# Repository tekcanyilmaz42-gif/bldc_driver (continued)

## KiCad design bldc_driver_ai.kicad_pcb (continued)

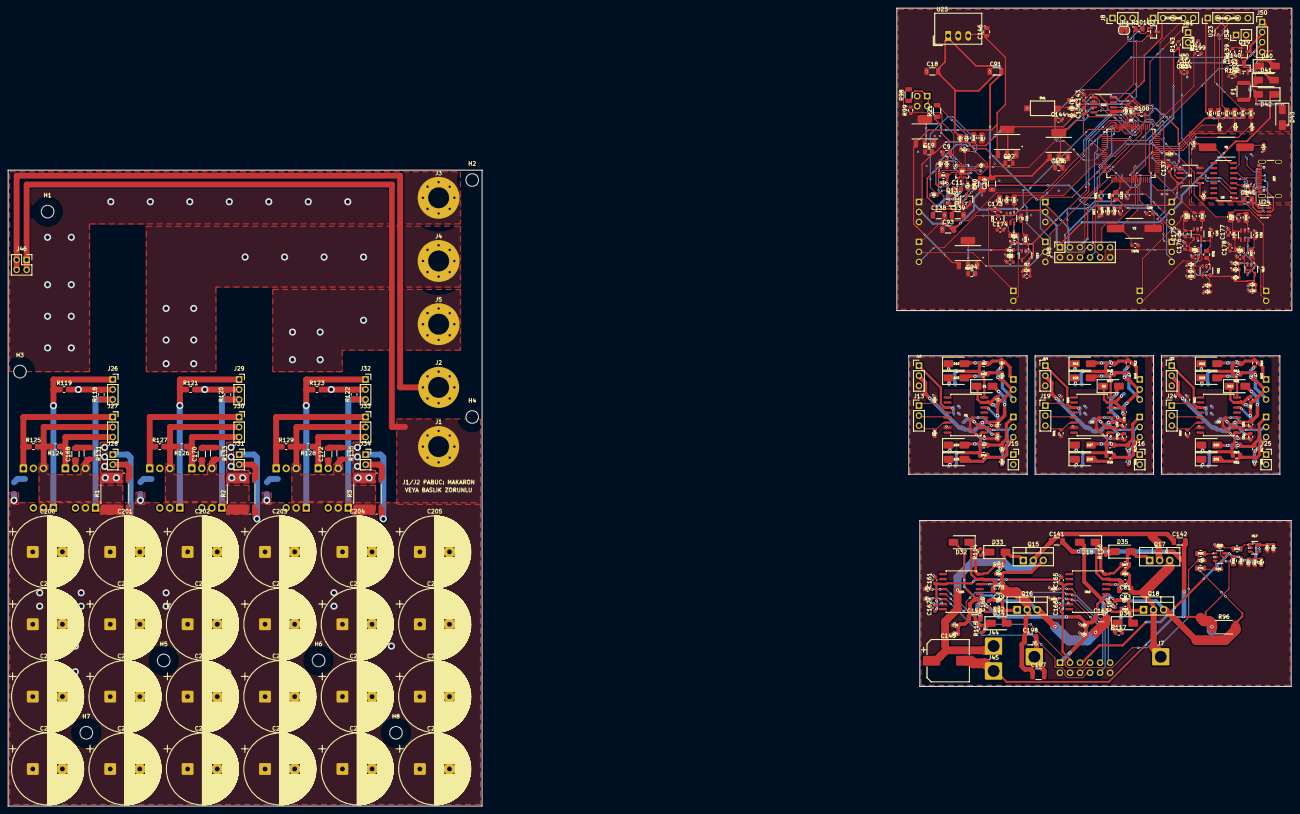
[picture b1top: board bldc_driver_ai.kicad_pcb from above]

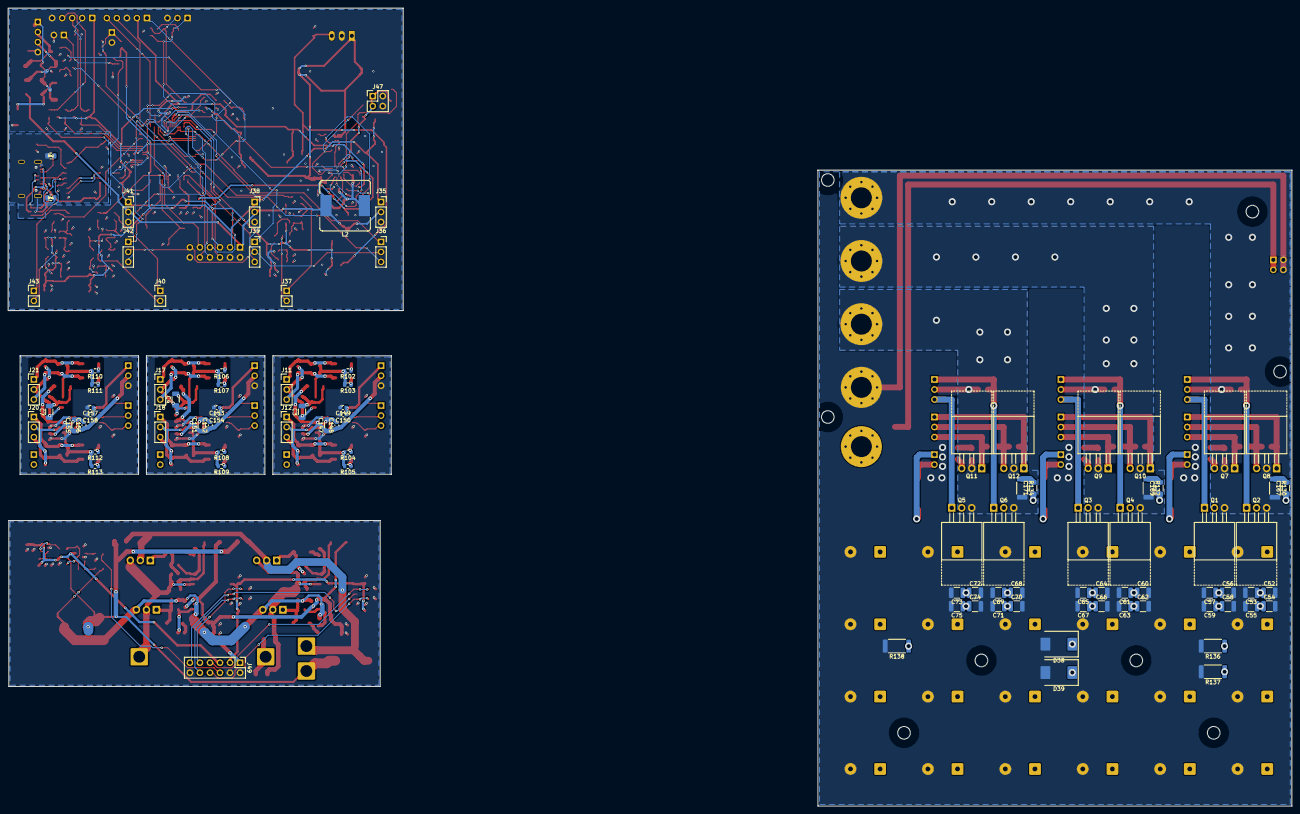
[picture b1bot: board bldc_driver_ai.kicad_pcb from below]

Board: 2 copper layers, 325.0 x 202.0 mm, 460 parts (94 on the bottom side), 177 nets.

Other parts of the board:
H1, H2, H3, H4, H5, H6, H7, H8: M3_Sogutucu; MountingHole_3.2mm_M3

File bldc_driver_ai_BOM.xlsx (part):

bldc_driver_ai – Malzeme Listesi (BOM)
Rev 2.5 (2 katman). Kaynak: bldc_driver_ai.kicad_pcb, referans format: yardımcı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
Üretilecek set sayısı: |  |  | 1 |  | Sarı hücreler (set sayısı, birim fiyat) kullanıcı girişidir. Yeşil = referans B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
şematik | footprint | No | Kart / Modül | Referanslar | Adet / set | Değer | Kılıf (footprint) | Üretici parça no (MPN) | Üretici | Açıklama | Tedarikçi | Ürün arama | Datasheet | Toplam adet | Birim fiyat (TL) | Toplam fiyat (TL) | Not
 |  |  | 1 - Güç kartı
 |  | 1 | Güç kartı | Q1, Q2, Q3, Q4, Q5, Q6, Q7, Q8, Q9, Q10, Q11, Q12 | 12 | IRFB4110PBF | TO-220-3_Horizontal_TabUp_NoHole | IRFB4110PBF | Infineon | N-kanal MOSFET 100 V, 4.5 mΩ, TO-220AB | DigiKey / Özdisan | DigiKey'de ara | irfb4110pbf.pdf |  |  |  | DI101N10PQ yerine (Rev 3.0). Güç kartında kartın altında yatık, tab soğutucuya 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
 |  | 2 | Güç kartı | D38, D39 | 2 | 5.0SMDJ58CA | D_SMC | 5.0SMDJ58CA | Littelfuse | TVS diyot 58 V çift yönlü 5000 W, SMC | DigiKey | DigiKey'de ara | 5.0SMDJ series datasheet |  |  |  | Referanstaki SMCJ58A yerine daha yüksek enerjili TVS (bara koruması, Faz 3)
 |  | 3 | Güç kartı | C52, C53, C54, C55, C56, C57, C58, C59, C60, C61, C62, C63, C64, C65, C66, C67,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 | 24 | 4.7uF/100V | C_1210 | HMK325C7475KN-TE | Taiyo Yuden | MLCC 4.7 µF 100 V X7S 1210 (bara seramik) | DigiKey | DigiKey'de ara | GRM32E datasheet |  |  |  | Faz başına yüksek frekans bara dekuplajı (Faz 3)
 |  | 4 | Güç kartı | C167, C168, C169, C170, C171, C172 | 6 | 4.7nF/100V C0G | C_1206 | GRM3195C2A472JA01D | Murata | MLCC 4.7 nF 100 V C0G 1206 (snubber) | DigiKey | DigiKey'de ara | GRM319 datasheet |  |  |  | RC snubber (Faz 3)
 |  | 5 | Güç kartı | C200, C201, C202, C203, C204, C205, C206, C207, C208, C209, C210, C211, C212, C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 | 24 | 1000uF/100V | CP_Radial_D18.0mm_L40mm_P7.50mm_KOSHIN_KLH | PKLH-100V102MK400 | KOSHIN | Alüminyum elektrolitik 1000 µF ±%20 100 V, KLH serisi, Ø18 x 40 mm radyal, P 7.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 | Özdisan | DigiKey'de ara | KLH-100V102MK400.pdf (KOSHIN DJJ-2875) |  |  |  | Kullanıcı seçimi: TDK B32776G4506 film yerine. Güç kartının sağ bölümünde, pete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
 |  | 6 | Güç kartı | R1, R2, R3 | 3 | 0.2mR 4-terminal | R_Shunt_Isabellenhuette_BVR4026 | BVR-Z-R0002-1.0 | Isabellenhütte | 4 uçlu (Kelvin) şönt 0.2 mΩ %1, 4026 | DigiKey / Mouser | DigiKey'de ara | BVR datasheet |  |  |  | Faz 3: HoLRS2512 yerine 4 uçlu şönt; 100 A rms'de I²R ≈ 2 W. MPN son ekini dist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
 |  | 7 | Güç kartı | R118, R119, R120, R121, R122, R123, R124, R125, R126, R127, R128, R129 | 12 | 10k | R_0805 | RC0603JR-0710KL | YAGEO | Direnç 10 kΩ %5 0603 | Özdisan | DigiKey'de ara | PYu-RC_Group_51_RoHS_L_10.pdf
 |  | 8 | Güç kartı | R130, R132, R134 | 3 | 2.2 | R_2010 | CRCW20102R20FKEF | Vishay | Direnç 2.2 Ω %1 0.75 W 2010 (yüksek taraf RC snubber) | DigiKey | DigiKey'de ara | dcrcwe3.pdf |  |  |  | HS snubber, alt yüzde band içinde; kayıp ≈ 0.27 W
 |  | 9 | Güç kartı | R131, R133, R135 | 3 | 2.2 | R_1210 | CRCW12102R20FKEA | Vishay | Direnç 2.2 Ω %1 0.5 W 1210 (alçak taraf RC snubber) | DigiKey | DigiKey'de ara | dcrcwe3.pdf |  |  |  | LS snubber; band üstüne sığması için 2010 yerine 1210 (kayıp ≈ 0.27 W)
 |  | 10 | Güç kartı | R136, R137, R138 | 3 | 10k 1W | R_2512 | CRCW251210K0FKEG | Vishay | Direnç 10 kΩ %1 1 W 2512 (bara deşarj) | DigiKey | DigiKey'de ara | dcrcwe3.pdf |  |  |  | Bara kapasitörü deşarj (bleeder), Faz 3
 |  | 11 | Güç kartı | J28, J31, J34 | 3 | - | PinSocket_1x02 | - | genel | 2.54 mm dişi soket 1x2, 8.5 mm gövde | genel (Motorobit / Özdisan) |  | - |  |  |  | Kartlar arası konnektör
 |  | 12 | Güç kartı | J26, J27, J29, J30, J32, J33 | 6 | - | PinSocket_1x03 | - | genel | 2.54 mm dişi soket 1x3, 8.5 mm gövde | genel (Motorobit / Özdisan) |  | - |  |  |  | Kartlar arası konnektör
 |  | 13 | Güç kartı | J46 | 1 | - | PinSocket_2x02 | - | genel | 2.54 mm dişi soket 2x2, 8.5 mm gövde – riser | genel (Motorobit / Özdisan) |  | - |  |  |  | Kartlar arası konnektör
 |  |  | 2 - Gate driver (U/V/W)
 |  | 14 | Gate driver (U/V/W) | U1, U2, U3 | 3 | IR2110S | SOIC-16W_7.5x10.3mm_P1.27mm | IR2110STRPBF | Infineon | Yüksek/alçak taraf gate sürücü, SOIC-16W | Motorobit | DigiKey'de ara | IR2110(-1-2)(S)PbF
 |  | 15 | Gate driver (U/V/W) | D10, D11, D12, D23, D24, D25, D26, D27, D28, D29, D30, D31 | 12 | SS18 | D_SMA | SS18 | onsemi | Schottky diyot 1 A 80 V, SMA | Özdisan | DigiKey'de ara | SK12-SK110 |  |  |  | VCC-VB (bootstrap) ve gate deşarj diyotu olarak kullanılıyor
 |  | 16 | Gate driver (U/V/W) | D1, D2, D13 | 3 | US1D | D_SMA | US1D-E3/61T | Vishay | Ultra hızlı diyot 1 A 200 V, SMA | DigiKey | DigiKey'de ara | US1A-US1M datasheet |  |  |  | Bootstrap diyodu (SS18 yerine, Faz 2)
 |  | 17 | Gate driver (U/V/W) | C1, C5, C6, C148, C149, C152, C153, C156, C157 | 9 | 100nF | C_0603 | CL10B104KB8NNNC | Samsung | MLCC 100 nF 50 V X7R 0603 | Özdisan | DigiKey'de ara | SAMSUNG MLCC_JAN-2024.pdf
 |  | 18 | Gate driver (U/V/W) | C3, C4, C7 | 3 | 2.2uF/25V | C_1206 | CL31B225KAHNNNE | Samsung | MLCC 2.2 µF 25 V X7R 1206 | Özdisan | DigiKey'de ara | SAMSUNG MLCC_JAN-2024.pdf |  |  |  | Revizyonla eklendi
 |  | 19 | Gate driver (U/V/W) | C41, C47, C48, C49, C50, C51, C150, C154, C158 | 9 | 1uF | C_0603 | C0603X5R105K250NT | OEM | MLCC 1 µF 25 V X5R 0603 | Özdisan | DigiKey'de ara | -
 |  | 20 | Gate driver (U/V/W) | C147, C151, C155 | 3 | 22uF/25V | C_1206 | CL31A226KAHNNNE | Samsung | MLCC 22 µF 25 V X5R 1206 | Özdisan | DigiKey'de ara | SAMSUNG MLCC_JAN-2024.pdf |  |  |  | Gate sürücü VCC dekuplajı
 |  | 21 | Gate driver (U/V/W) | R6, R7, R10, R11, R14, R15, R43, R45, R47, R48, R51, R52 | 12 | 10 | R_0805 | 0805S8J0100T5E | ROYALOHM | Direnç 10 Ω %5 0805 (gate direnci) | Özdisan | DigiKey'de ara | general_royalohm.pdf
 |  | 22 | Gate driver (U/V/W) | R8, R9, R12, R13, R16, R17, R44, R46, R49, R50, R53, R54, R58, R59, R60, R61, R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 | 18 | 10k | R_0603 | RC0603JR-0710KL | YAGEO | Direnç 10 kΩ %5 0603 | Özdisan | DigiKey'de ara | PYu-RC_Group_51_RoHS_L_10.pdf
 |  | 23 | Gate driver (U/V/W) | R102, R103, R104, R105, R106, R107, R108, R109, R110, R111, R112, R113 | 12 | 2.2 | R_0603 | WR06X2R2 JGL | WALSIN | Direnç 2.2 Ω %5 0603 | Özdisan | DigiKey'de ara | ASC_WR_V32
 |  | 24 | Gate driver (U/V/W) | J10, J11, J12, J13, J14, J17, J18, J19, J20, J21, J22, J24 | 12 | - | PinHeader_1x03 | - | genel | 2.54 mm erkek pin başlık 1x3, düz | genel (Motorobit / Özdisan) |  | - |  |  |  | Kartlar arası konnektör
 |  | 25 | Gate driver (U/V/W) | J15, J16, J25 | 3 | - | PinSocket_1x02 | ESQ-102-xx-T-S sınıfı (uzun kuyruklu) | Samtec / genel | 2.54 mm 1x2 STACKING dişi soket: üstte 8.5 mm soket, altta ≥ 10.5 mm uzun kuyru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 | Samtec / LCSC | DigiKey'de ara | - |  |  |  | Faz 7 (inceleme K21): şönt ölçüm hattı güç kartı J28/J31/J34 soketlerine bu kuy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
 |  |  | 3 - Kontrol kartı
 |  | 26 | Kontrol kartı | Q13, Q14 | 2 | IRLML0100TRPBF | SOT-23 | IRLML0100TRPBF | Infineon | N-kanal MOSFET 100 V 1.6 A, SOT-23 | DigiKey | DigiKey'de ara | IRLML0100 datasheet |  |  |  | Faz 2
 |  | 27 | Kontrol kartı | Q19, Q20 | 2 | AO3400A | SOT-23 | AO3400A | Alpha & Omega | N-kanal MOSFET 30 V 5.7 A, SOT-23 | DigiKey | DigiKey'de ara | AO3400A datasheet |  |  |  | Kontaktör / ön şarj sürücüsü
 |  | 28 | Kontrol kartı | U4 | 1 | ADuM1201 | ADuM1201_LP | ADUM1201ARZ | Analog Devices | Çift kanallı dijital izolatör, SOIC-8 | DigiKey | DigiKey'de ara | ADuM1200/ADuM1201 (Rev.L) |  |  |  | Referans BOM'da CJMCU-1201 modülü var; kart üstü SOIC-8 entegre gerekir
 |  | 29 | Kontrol kartı | U5 | 1 | CH340G | CH340G_LP | CH340G | WCH | USB-UART dönüştürücü, SOP-16 | Motorobit | DigiKey'de ara | ch340g-datasheet
 |  | 30 | Kontrol kartı | U6 | 1 | dsPIC33CK256MP508 | LQFP-80_12x12mm_P0.5mm | DSPIC33CK256MP508-I/PT | Microchip Technology | dsPIC33CK DSC, 256 KB, TQFP-80 12x12 | DigiKey | DigiKey'de ara | dsPIC33CK256MP508 Family Data Sheet |  |  |  | Referans BOM'da MP506 (64 pin) yazıyor; tasarım 80 pinli MP508 kullanıyor
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
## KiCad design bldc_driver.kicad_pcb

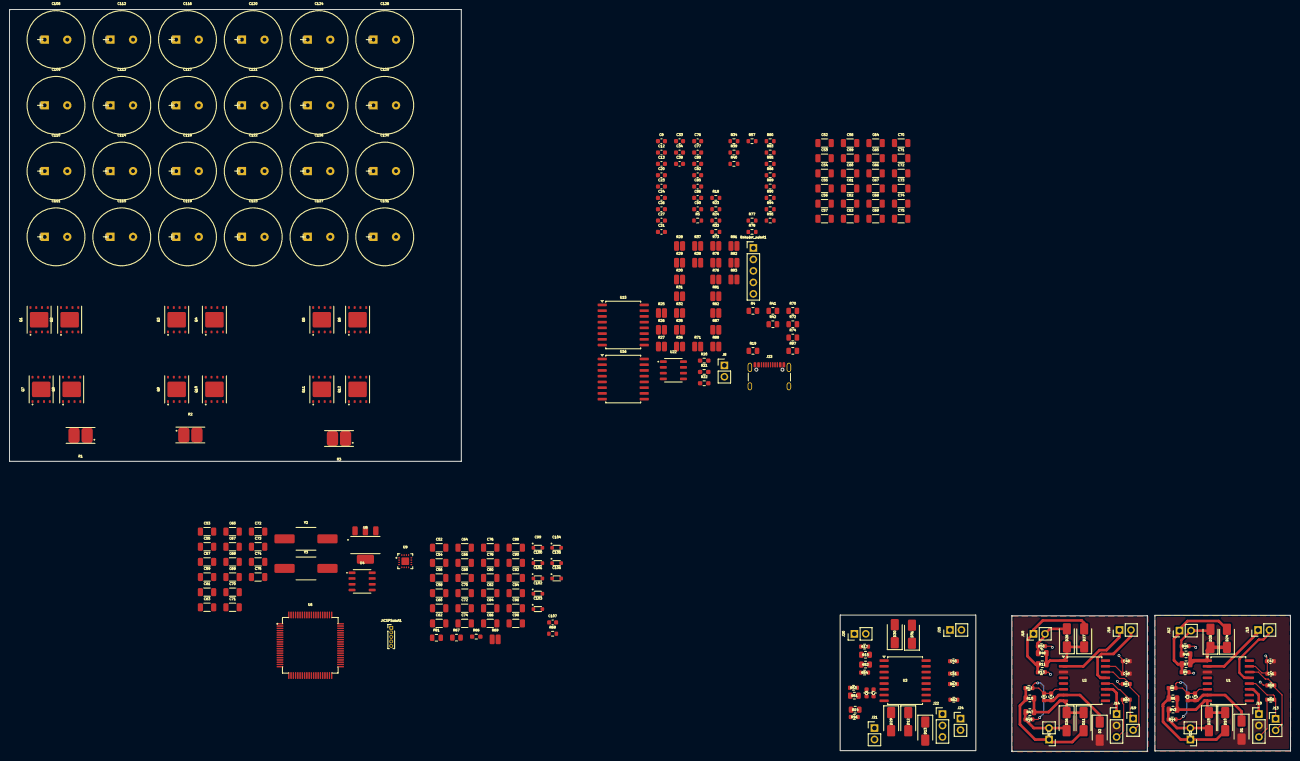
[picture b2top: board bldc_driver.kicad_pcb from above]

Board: 2 copper layers, 283.5 x 164.2 mm, 277 parts (0 on the bottom side), 102 nets.

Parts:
C1, C5, C6: 100nF; C_0603_1608Metric
C3, C4, C7: 10uF; C_0603_1608Metric
C8: 10nF; C_0603_1608Metric
C12: 4.7nF; C_0603_1608Metric
C13, C20, C31, C38, C41, C47, C48, C49, C50, C51, C76#2, C77, C80#2, C82#2, C90, C107: 1uF; C_0603_1608Metric
C23, C24, C26, C27, C33, C34, C85, C86: 1nF; C_0603_1608Metric
C52, C52#2, C53, C53#2, C54, C54#2, C55, C55#2, C56, C56#2, C57, C57#2, C58, C58#2, C59, C59#2, C60, C60#2, C61, C61#2, C62, C62#2, C63, C63#2, C64, C64#2, C65, C65#2, C66, C66#2, C67, C67#2, C68, C68#2, C68#3, C69, C69#2, C70, C70#2, C70#3, C71, C71#2, C72, C72#2, C72#3, C73, C73#2, C74, C74#2, C74#3, C75, C75#2, C76, C78, C80, C82, C84, C86#2, C88, C90#2, C92, C94, C96, C98: 2.2uF; C_1206_3216Metric
C99, C101: 20pF; CL10B104KB8NNNC
C100, C102, C103, C104, C105, C106: 100nF; CL10B104KB8NNNC
C108, C109, C110, C111, C112, C113, C114, C115, C116, C117, C118, C119, C120, C121, C122, C123, C124, C125, C126, C127, C128, C129, C130, C131: 470uF; KLH-063V471MH200-TA5.0
D1, D2, D10, D11, D12, D13, D23, D24, D25, D26, D27, D28, D29, D30, D31: SS18; D_SMA
Enkoder_soket1: Conn_01x05_Socket; PinHeader_1x05_P2.54mm_Vertical
FB1: FerriteBead; C_0805_2012Metric
J8: CAN-bus; PinHeader_1x02_P2.54mm_Vertical
J10, J14, J22: Conn_01x03_Pin; PinHeader_1x03_P2.54mm_Vertical
J11, J12, J13, J15, J16, J17, J18, J19, J20, J21, J24, J25: Conn_01x02_Pin; PinHeader_1x02_P2.54mm_Vertical
J23: USB_IN; USB_C_Receptacle_GCT_USB4105-xx-A_16P_TopMnt_Horizontal
JICSPSoket1: Conn_01x05_Pin; PinHeader_1x05_P1.00mm_Vertical
Q1, Q2, Q3, Q4, Q5, Q6, Q7, Q8, Q9, Q10, Q11, Q12: DI101N10PQ
R1, R2, R3: HoLRS2512
R4, R70, R72, R74: 1.5k; R_0805_2012Metric
R5: 36k; R_0603_1608Metric
R6, R7, R10, R11, R14, R15, R43, R45, R47, R48, R51, R52: 10; R_0805_2012Metric
R8, R9, R12, R13, R16, R17, R23, R24, R33, R34, R39, R40, R44, R46, R49, R50, R53, R54, R57, R58, R59, R60, R61, R62, R63, R68, R77, R78, R80, R83, R85, R86, R89, R90, R94, R95: 10k; R_0603_1608Metric
R18: 20k; R_0603_1608Metric
R19, R67, R97: 1k; R_0805_2012Metric
R20: 2.2; R_0603_1608Metric_Pad0.98x0.95mm_HandSolder
R21, R66: 100k; R_0603_1608Metric_Pad0.98x0.95mm_HandSolder
R22: 60k; R_0603_1608Metric_Pad0.98x0.95mm_HandSolder
R25, R26, R27, R29, R30, R31, R35, R36, R37, R76, R81, R82, R87, R88, R91, R92: 10; R_0508_1220Metric_Pad1.12x2.15mm_HandSolder
R28, R32, R38, R69, R71, R73, R75, R93: 100; R_0508_1220Metric_Pad1.12x2.15mm_HandSolder
R41, R42: 5.1k; R_0805_2012Metric
U1, U2, U3, U15, U16: IR2110S; SOIC-16W_7.5x10.3mm_P1.27mm
U4: ADuM1201
U6: dsPIC33CK256MP508
U8: NCP1117
U9: MIC2128
U22: TJA1051
Y2, Y3: 12MHz Kristal; AS-12.000-18-3030-EXT-SMD-TR

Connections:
3V3: C20.2, C31.2, C38.2, C90.2, C102.2, C103.2, C104.2, C105.2, C106.2, C107.2, Enkoder_soket1.1, FB1.1, J10.1, J14.1, J22.1, JICSPSoket1.2, R23.2, R33.2, R39.2, R57.1, R68.2, R70.1, R72.1, R74.1, R94.2, U1.11 (VDD), U2.11 (VDD), U3.11 (VDD), U4.8 (VDD2), U6.12 (VDD), U6.31 (VDD), U6.51 (VDD), U6.71 (VDD), U8.2 (VO), U8.4 (TAB), U15.11 (VDD), U16.11 (VDD), U22.5 (VIO)
5V: J23.A4 (VBUS), J23.A9 (VBUS), J23.B4 (VBUS), J23.B9 (VBUS), U4.1 (VDD1)
12V: C13.2, C41.2, C47.2, C48.2, C49.2, C50.2, C51.2, C76#2.2, C77.2, C80#2.2, C82#2.2, D1.2 (A), D2.2 (A), D13.2 (A), J10.2, J14.2, J22.2, U1.3 (VCC), U2.3 (VCC), U3.3 (VCC), U9.9 (EXTVDD), U15.3 (VCC), U16.3 (VCC)
CANH: J8.2, U22.7 (CANH)
CANL: J8.1, U22.6 (CANL)
Enkoder_A: R71.2, U6.54 (RD5/RP69)
Enkoder_A_soket: Enkoder_soket1.2, R70.2, R71.1
Enkoder_B: R73.2, U6.53 (RD6/RP70)
Enkoder_B_soket: Enkoder_soket1.3, R72.2, R73.1
Enkoder_Z: R75.2, U6.52 (RD7/RP71)
Enkoder_Z_soket: Enkoder_soket1.4, R74.2, R75.1
FB: C12.1, R5.1, R18.1, R19.2, U9.13 (FB)
GND_PC: C99.1, C101.1, J23.A1 (GND), J23.A12 (GND), J23.B1 (GND), J23.B12 (GND), R41.1, R42.1, U4.4 (GND1)
G_UH1: D10.2 (A), J11.1, Q1.4 (G), R6.2, R8.2
G_UH2: D23.2 (A), J11.2, Q2.4 (G), R43.2, R44.2
G_UH_IN: J13.1, R59.1, U1.12 (HIN), U6.4 (RE1)
G_UL1: D24.2 (A), J12.1, Q7.4 (G), R7.2, R9.2
G_UL2: D25.2 (A), J12.2, Q8.4 (G), R45.2, R46.2
G_UL_IN: J13.2, R58.2, U1.14 (LIN), U6.2 (RE0)
G_VH1: D11.2 (A), J17.1, Q3.4 (G), R10.2, R12.2
G_VH2: D26.2 (A), J17.2, Q4.4 (G), R47.2, R49.2
G_VH_IN: J19.1, R60.1, U2.12 (HIN), U6.19 (RE3)
G_VL1: D27.2 (A), J18.1, Q9.4 (G), R11.2, R13.2
G_VL2: D28.2 (A), J18.2, Q10.4 (G), R48.2, R50.2
G_VL_IN: J19.2, R61.2, U2.14 (LIN), U6.17 (RE2)
G_WH1: D12.2 (A), J21.1, Q5.4 (G), R14.2, R16.2
G_WH2: D29.2 (A), J21.2, Q6.4 (G), R51.2, R53.2
G_WH_IN: J24.1, R62.1, U3.12 (HIN), U6.24 (RE5)
G_WL1: D30.2 (A), J20.1, Q11.4 (G), R15.2, R17.2
G_WL2: D31.2 (A), J20.2, Q12.4 (G), R52.2, R54.2
G_WL_IN: J24.2, R63.2, U3.14 (LIN), U6.22 (RE4)
IF_L: C8.1, C13.1, C20.1, C24.1, C27.1, C31.1, C34.1, C38.1, C41.1, C47.1, C48.1, C49.1, C50.1, C51.1, C52.2, C53.2, C54.2, C55.2, C56.2, C57.2, C58#2.2, C59.2, C60.2, C61.2, C62#2.2, C63.2, C64.2, C65#2.2, C66.2, C67.2, C68#2.2, C69#2.2, C70#3.2, C71#2.2, C72#3.2, C73.2, C74#3.2, C75.2, C76#2.1, C77.1, C80#2.1, C82#2.1, C86.1, C90.1, C100.1, C102.1, C103.1, C104.1, C105.1, C106.1, C107.1, Enkoder_soket1.5, J10.3, J14.3, J22.3, JICSPSoket1.3, R9.1, R13.1, R17.1, R21.1, R22.1, R24.1, R27.2, R30.2, R34.1, R36.2, R40.1, R46.1, R50.1, R54.1, R58.1, R59.2, R60.2, R61.1, R62.2, R63.1, R67.1, R77.2, R78.1, R80.2, R83.1, R85.1, R86.1, R89.1, R90.1, R91.2, R95.1, R97.1, U1.15 (VSS), U2.15 (VSS), U3.15 (VSS), U4.5 (GND2), U6.11 (VSS), U6.26 (AVSS), U6.32 (VSS), U6.50 (VSS), U6.70 (VSS), U8.1 (GND/ADJ), U9.6 (PGND), U9.14 (AGND), U9.17 (EP), U15.15 (VSS), U16.15 (VSS), U22.2 (GND), U22.8 (S)
IN181_IFout: C86.2, R93.1, U6.23 (RA4)
IN181_Uout: C24.2, R28.1, U6.16 (RA0)
IN181_Vout: C27.2, R32.1, U6.41 (RB2/RP34)
IN181_Wout: C34.2, R38.1, U6.58 (RB7/RP39)
MCLR: JICSPSoket1.1, R69.1, U6.9 (MCLR)
unnamed: C12.2, R18.2
unnamed: C1.2, C3.2, D1.1 (K), U1.7 (VB)
unnamed: C4.2, C5.2, D2.1 (K), U2.7 (VB)
unnamed: D10.1 (K), D23.1 (K), R6.1, R43.1, U1.8 (HO)
unnamed: D11.1 (K), D26.1 (K), R10.1, R47.1, U2.8 (HO)
unnamed: D12.1 (K), D29.1 (K), R14.1, R51.1, U3.8 (HO)
unnamed: C6.2, C7.2, D13.1 (K), U3.7 (VB)
unnamed: D24.1 (K), D25.1 (K), R7.1, R45.1, U1.1 (LO)
unnamed: D27.1 (K), D28.1 (K), R11.1, R48.1, U2.1 (LO)
unnamed: D30.1 (K), D31.1 (K), R15.1, R52.1, U3.1 (LO)
unnamed: R81.2, R85.2
unnamed: R81.1, U15.8 (HO)
unnamed: R82.2, R86.2
unnamed: R82.1, U15.1 (LO)
unnamed: R87.2, R89.2
unnamed: R87.1, U16.8 (HO)
unnamed: R88.2, R90.2
unnamed: R88.1, U16.1 (LO)
unnamed: J23.A5 (CC1), R41.2
unnamed: J23.B5 (CC2), R42.2
unnamed: R4.2, U9.3 (SW)
unnamed: R19.1, R97.2
unnamed: R68.1, R69.2
unnamed: J23.A6 (D+), J23.B6 (D+)
unnamed: J23.A7 (D-), J23.B7 (D-)
unnamed: FB1.2, U6.25 (AVDD)
unnamed: C23.2, R26.1
unnamed: C23.1, R27.1
unnamed: R21.2, R22.2, U9.11 (FREQ)
unnamed: R4.1, U9.2 (ILIM)
unnamed: R20.1, U9.8 (PVDD)
unnamed: C8.2, U9.12 (SS)
unnamed: R20.2, U9.15 (VDD)
unnamed: C26.2, R29.1
unnamed: C26.1, R30.1
unnamed: C33.2, R35.1
unnamed: C33.1, R36.1
unnamed: C85.2, R76.1
unnamed: C85.1, R91.1
OSCI_DSP: C101.2, U6.34 (OSCI/CLKI), Y3.2
OSCO_DSP: C99.2, U6.35 (OSCO/CLKO), Y3.1
PGC1: JICSPSoket1.5, U6.61 (RB9/RP41)
PGD1: JICSPSoket1.4, U6.60 (RB8/RP40)
Phase_U: C1.1, C3.1, Q1.1 (S), Q1.2 (S), Q1.3 (S), Q2.1 (S), Q2.2 (S), Q2.3 (S), Q7.5 (D), Q7.6 (D), Q7.7 (D), Q7.8 (D), Q7.9 (D), Q8.5 (D), Q8.6 (D), Q8.7 (D), Q8.8 (D), Q8.9 (D), R8.1, R44.1, U1.6 (VS)
Phase_V: C4.1, C5.1, Q3.1 (S), Q3.2 (S), Q3.3 (S), Q4.1 (S), Q4.2 (S), Q4.3 (S), Q9.5 (D), Q9.6 (D), Q9.7 (D), Q9.8 (D), Q9.9 (D), Q10.5 (D), Q10.6 (D), Q10.7 (D), Q10.8 (D), Q10.9 (D), R12.1, R49.1, U2.6 (VS)
Phase_W: C6.1, C7.1, Q5.1 (S), Q5.2 (S), Q5.3 (S), Q6.1 (S), Q6.2 (S), Q6.3 (S), Q11.5 (D), Q11.6 (D), Q11.7 (D), Q11.8 (D), Q11.9 (D), Q12.5 (D), Q12.6 (D), Q12.7 (D), Q12.8 (D), Q12.9 (D), R16.1, R53.1, U3.6 (VS)
RXD_DSP: U4.7 (VOA), U6.46 (RC8/RP56)
RXD_DSP_can: U6.76 (RB11/RP43), U22.4 (RXD)
SD: J15.2, J16.2, J25.2, R57.2, U1.13 (SD), U2.13 (SD), U3.13 (SD), U6.74 (RD0/RP64), U15.13 (SD), U16.13 (SD)
TLV_IN+_IF: R94.1, R95.2
TLV_IN+_u: R23.1, R24.2
TLV_IN+_v: R33.1, R34.2
TLV_IN+_w: R39.1, R40.2
TXD_DSP: U4.6 (VOB), U6.47 (RC9/RP57)
TXD_DSP_can: U6.75 (RB10/RP42), U22.1 (TXD)
USH: J15.1, Q7.1 (S), Q7.2 (S), Q7.3 (S), Q8.1 (S), Q8.2 (S), Q8.3 (S), R1.2, R26.2, U1.2 (COM)
USL: C52#2.2, C53#2.2, C54#2.2, C55#2.2, C56#2.2, C57#2.2, C58.2, C59#2.2, C60#2.2, C61#2.2, C62.2, C63#2.2, C64#2.2, C65.2, C66#2.2, C67#2.2, C68.2, C68#3.2, C69.2, C70.2, C70#2.2, C71.2, C72.2, C72#2.2, C73#2.2, C74.2, C74#2.2, C75#2.2, C76.2, C78.2, C80.2, C82.2, C84.2, C86#2.2, C88.2, C90#2.2, C92.2, C94.2, C96.2, C98.2, C108.1 (+), C109.1 (+), C110.1 (+), C111.1 (+), C112.1 (+), C113.1 (+), C114.1 (+), C115.1 (+), C116.1 (+), C117.1 (+), C118.1 (+), C119.1 (+), C120.1 (+), C121.1 (+), C122.1 (+), C123.1 (+), C124.1 (+), C125.1 (+), C126.1 (+), C127.1 (+), C128.1 (+), C129.1 (+), C130.1 (+), C131.1 (+), R1.1, R2.1, R3.1
VBAT: C52.1, C52#2.1, C53.1, C53#2.1, C54.1, C54#2.1, C55.1, C55#2.1, C56.1, C56#2.1, C57.1, C57#2.1, C58.1, C58#2.1, C59.1, C59#2.1, C60.1, C60#2.1, C61.1, C61#2.1, C62.1, C62#2.1, C63.1, C63#2.1, C64.1, C64#2.1, C65.1, C65#2.1, C66.1, C66#2.1, C67.1, C67#2.1, C68.1, C68#2.1, C68#3.1, C69.1, C69#2.1, C70.1, C70#2.1, C70#3.1, C71.1, C71#2.1, C72.1, C72#2.1, C72#3.1, C73.1, C73#2.1, C74.1, C74#2.1, C74#3.1, C75.1, C75#2.1, C76.1, C78.1, C80.1, C82.1, C84.1, C86#2.1, C88.1, C90#2.1, C92.1, C94.1, C96.1, C98.1, C108.2 (-), C109.2 (-), C110.2 (-), C111.2 (-), C112.2 (-), C113.2 (-), C114.2 (-), C115.2 (-), C116.2 (-), C117.2 (-), C118.2 (-), C119.2 (-), C120.2 (-), C121.2 (-), C122.2 (-), C123.2 (-), C124.2 (-), C125.2 (-), C126.2 (-), C127.2 (-), C128.2 (-), C129.2 (-), C130.2 (-), C131.2 (-), Q1.5 (D), Q1.6 (D), Q1.7 (D), Q1.8 (D), Q1.9 (D), Q2.5 (D), Q2.6 (D), Q2.7 (D), Q2.8 (D), Q2.9 (D), Q3.5 (D), Q3.6 (D), Q3.7 (D), Q3.8 (D), Q3.9 (D), Q4.5 (D), Q4.6 (D), Q4.7 (D), Q4.8 (D), Q4.9 (D), Q5.5 (D), Q5.6 (D), Q5.7 (D), Q5.8 (D), Q5.9 (D), Q6.5 (D), Q6.6 (D), Q6.7 (D), Q6.8 (D), Q6.9 (D), R66.1, U9.10 (EN), U9.16 (VIN)
VSH: J16.1, Q9.1 (S), Q9.2 (S), Q9.3 (S), Q10.1 (S), Q10.2 (S), Q10.3 (S), R2.2, R29.2, U2.2 (COM), U15.2 (COM), U16.2 (COM)
V_BUS_SENSE: C100.2, R66.2, R67.2, U6.21 (RA3)
WSH: J25.1, Q11.1 (S), Q11.2 (S), Q11.3 (S), Q12.1 (S), Q12.2 (S), Q12.3 (S), R3.2, R35.2, U3.2 (COM)
primer_1_H: R77.1, U6.39 (RE7), U15.12 (HIN)
primer_1_L: R78.2, U6.37 (RE6), U15.14 (LIN)
primer_2_H: R80.1, U6.44 (RE9), U16.12 (HIN)
primer_2_L: R83.2, U6.42 (RE8), U16.14 (LIN)

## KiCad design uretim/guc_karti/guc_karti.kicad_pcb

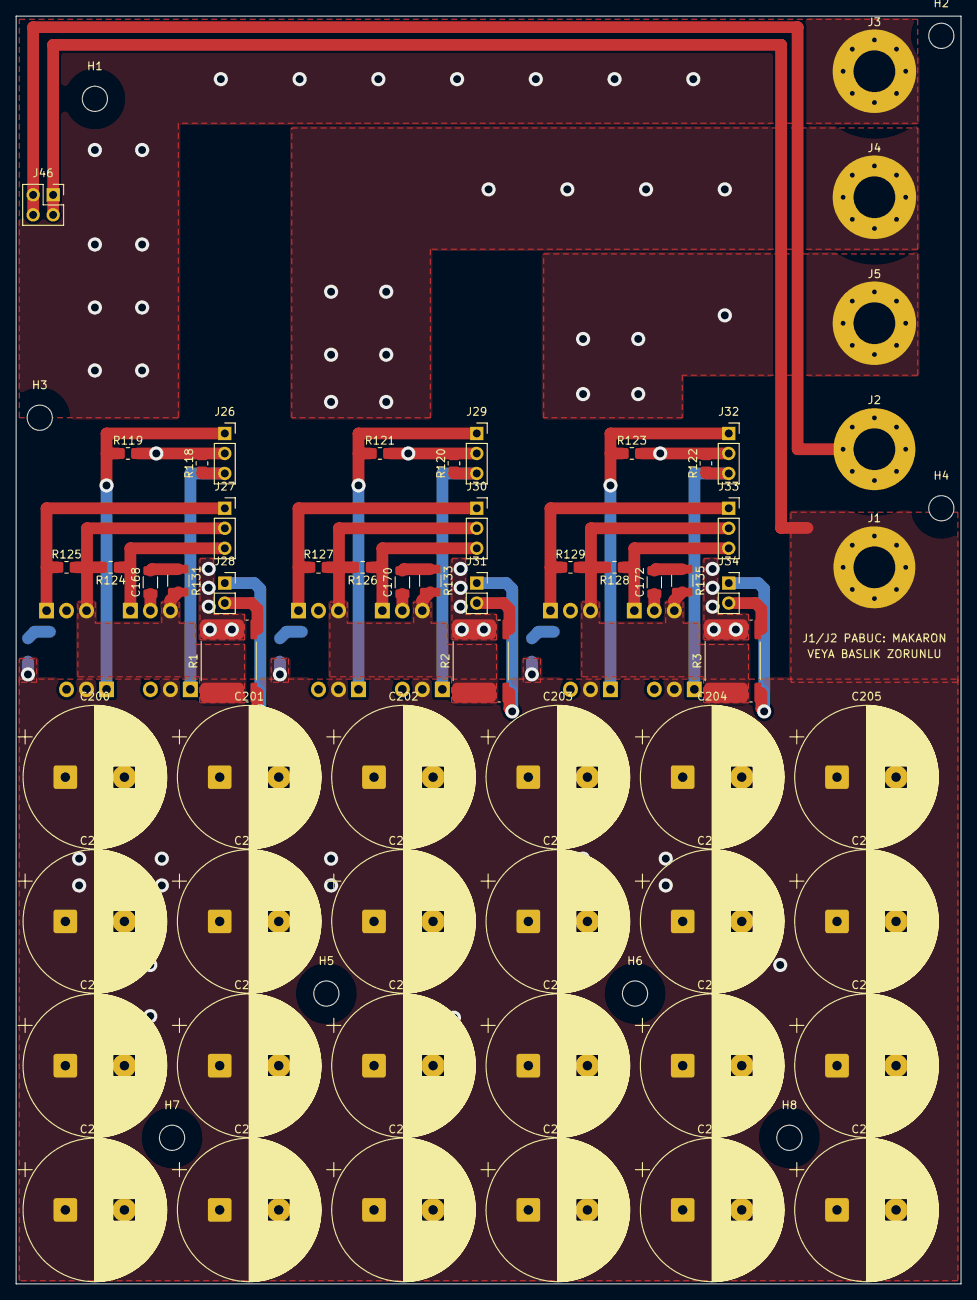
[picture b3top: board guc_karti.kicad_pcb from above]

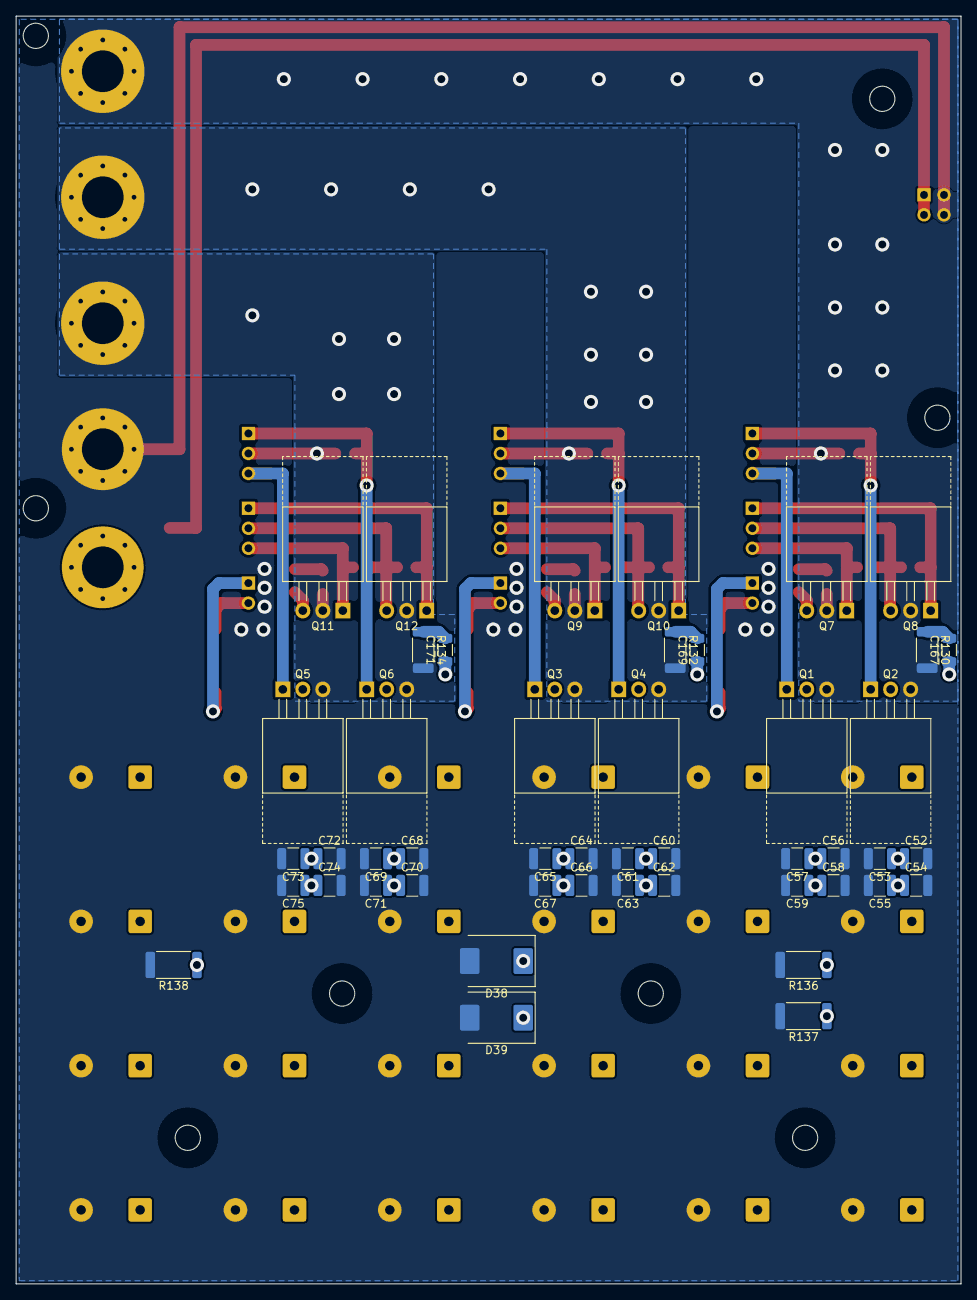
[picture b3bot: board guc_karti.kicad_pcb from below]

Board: 2 copper layers, 120.0 x 161.0 mm, 115 parts (47 on the bottom side), 32 nets.

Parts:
C52, C53, C54, C55, C56, C57, C58, C59, C60, C61, C62, C63, C64, C65, C66, C67, C68, C69, C70, C71, C72, C73, C74, C75: 4.7uF/100V; C_1210_3225Metric
C167, C168, C169, C170, C171, C172: 4.7nF/100V C0G; C_1206_3216Metric
C200, C201, C202, C203, C204, C205, C206, C207, C208, C209, C210, C211, C212, C213, C214, C215, C216, C217, C218, C219, C220, C221, C222, C223: 1000uF/100V; CP_Radial_D18.0mm_L40mm_P7.50mm_KOSHIN_KLH
D38, D39: 5.0SMDJ58CA; D_SMC
H1, H2, H3, H4, H5, H6, H7, H8: M3_Sogutucu; MountingHole_3.2mm_M3
J1: M5_Lug_VBAT; MountingHole_5.3mm_M5_Pad_Via
J2: M5_Lug_GND; MountingHole_5.3mm_M5_Pad_Via
J3: M5_Lug_U; MountingHole_5.3mm_M5_Pad_Via
J4: M5_Lug_V; MountingHole_5.3mm_M5_Pad_Via
J5: M5_Lug_W; MountingHole_5.3mm_M5_Pad_Via
J26: Gate_H_U; PinSocket_1x03_P2.54mm_Vertical
J27: Gate_L_U; PinSocket_1x03_P2.54mm_Vertical
J28: Sense_U; PinSocket_1x02_P2.54mm_Vertical
J29: Gate_H_V; PinSocket_1x03_P2.54mm_Vertical
J30: Gate_L_V; PinSocket_1x03_P2.54mm_Vertical
J31: Sense_V; PinSocket_1x02_P2.54mm_Vertical
J32: Gate_H_W; PinSocket_1x03_P2.54mm_Vertical
J33: Gate_L_W; PinSocket_1x03_P2.54mm_Vertical
J34: Sense_W; PinSocket_1x02_P2.54mm_Vertical
J46: Riser_VBAT_GND; PinSocket_2x02_P2.54mm_Vertical
Q1, Q2, Q3, Q4, Q5, Q6, Q7, Q8, Q9, Q10, Q11, Q12: IRFB4110PBF; TO-220-3_Horizontal_TabUp_NoHole
R1, R2, R3: 0.2mR 4-terminal; R_Shunt_Isabellenhuette_BVR4026
R118, R119, R120, R121, R122, R123, R124, R125, R126, R127, R128, R129: 10k; R_0805_2012Metric
R130, R132, R134: 2.2; R_2010_5025Metric
R131, R133, R135: 2.2; R_1210_3225Metric
R136, R137, R138: 10k 1W; R_2512_6332Metric

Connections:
/Katman1_Guc_Karti/SNB_UH: C167.2, R130.1
/Katman1_Guc_Karti/SNB_UL: C168.2, R131.1
/Katman1_Guc_Karti/SNB_VH: C169.2, R132.1
/Katman1_Guc_Karti/SNB_VL: C170.2, R133.1
/Katman1_Guc_Karti/SNB_WH: C171.2, R134.1
/Katman1_Guc_Karti/SNB_WL: C172.2, R135.1
GND: C52.2, C53.2, C54.2, C55.2, C56.2, C57.2, C58.2, C59.2, C60.2, C61.2, C62.2, C63.2, C64.2, C65.2, C66.2, C67.2, C68.2, C69.2, C70.2, C71.2, C72.2, C73.2, C74.2, C75.2, C200.2, C201.2, C202.2, C203.2, C204.2, C205.2, C206.2, C207.2, C208.2, C209.2, C210.2, C211.2, C212.2, C213.2, C214.2, C215.2, C216.2, C217.2, C218.2, C219.2, C220.2, C221.2, C222.2, C223.2, D38.2 (A2), D39.2 (A2), J2.1 (Pin_1_1), J46.2, J46.4, R1.4, R2.4, R3.4, R136.2, R137.2, R138.2
G_UH1: J26.1, Q2.1, R119.1
G_UH2: J26.3, Q1.1, R118.1
G_UL1: J27.1, Q8.1, R125.1
G_UL2: J27.3, Q7.1, R124.1
G_VH1: J29.1, Q4.1, R121.1
G_VH2: J29.3, Q3.1, R120.1
G_VL1: J30.1, Q10.1, R127.1
G_VL2: J30.3, Q9.1, R126.1
G_WH1: J32.1, Q6.1, R123.1
G_WH2: J32.3, Q5.1, R122.1
G_WL1: J33.1, Q12.1, R129.1
G_WL2: J33.3, Q11.1, R128.1
Phase_U: C168.1, J3.1 (Pin_1_1), J26.2, Q1.3, Q2.3, Q7.2, Q8.2, R118.2, R119.2, R130.2
Phase_V: C170.1, J4.1 (Pin_1_1), J29.2, Q3.3, Q4.3, Q9.2, Q10.2, R120.2, R121.2, R132.2
Phase_W: C172.1, J5.1 (Pin_1_1), J32.2, Q5.3, Q6.3, Q11.2, Q12.2, R122.2, R123.2, R134.2
USH: J27.2, Q7.3, Q8.3, R1.1, R124.2, R125.2, R131.2
U_SNS_N: J28.2, R1.3
U_SNS_P: J28.1, R1.2
VBAT: C52.1, C53.1, C54.1, C55.1, C56.1, C57.1, C58.1, C59.1, C60.1, C61.1, C62.1, C63.1, C64.1, C65.1, C66.1, C67.1, C68.1, C69.1, C70.1, C71.1, C72.1, C73.1, C74.1, C75.1, C167.1, C169.1, C171.1, C200.1, C201.1, C202.1, C203.1, C204.1, C205.1, C206.1, C207.1, C208.1, C209.1, C210.1, C211.1, C212.1, C213.1, C214.1, C215.1, C216.1, C217.1, C218.1, C219.1, C220.1, C221.1, C222.1, C223.1, D38.1 (A1), D39.1 (A1), J1.1 (Pin_1_1), J46.1, J46.3, Q1.2, Q2.2, Q3.2, Q4.2, Q5.2, Q6.2, R136.1, R137.1, R138.1
VSH: J30.2, Q9.3, Q10.3, R2.1, R126.2, R127.2, R133.2
V_SNS_N: J31.2, R2.3
V_SNS_P: J31.1, R2.2
WSH: J33.2, Q11.3, Q12.3, R3.1, R128.2, R129.2, R135.2
W_SNS_N: J34.2, R3.3
W_SNS_P: J34.1, R3.2

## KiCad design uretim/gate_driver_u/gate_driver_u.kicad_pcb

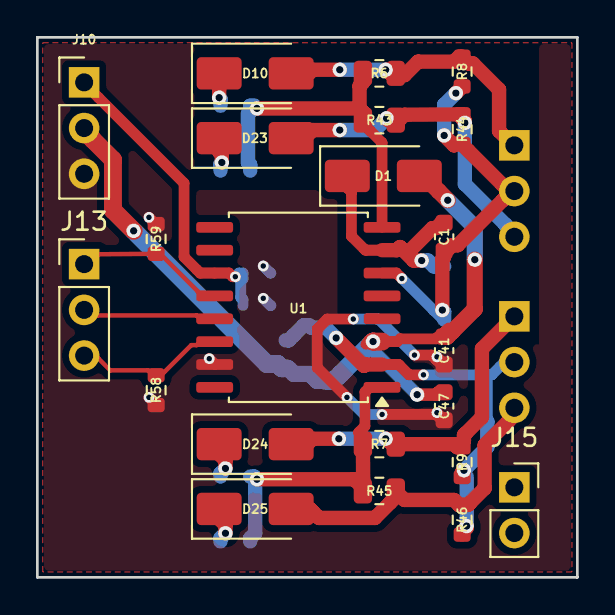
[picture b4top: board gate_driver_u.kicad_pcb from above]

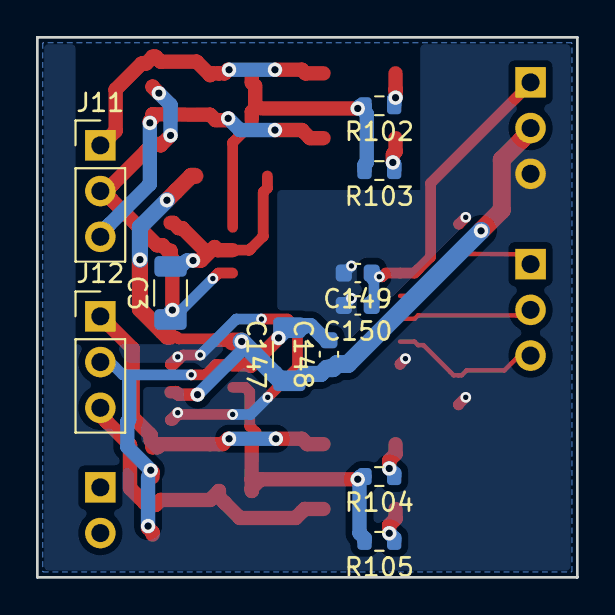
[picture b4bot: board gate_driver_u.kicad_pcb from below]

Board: 2 copper layers, 30.0 x 30.0 mm, 33 parts (11 on the bottom side), 19 nets.

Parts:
C1, C148, C149: 100nF; C_0603_1608Metric
C3: 2.2uF/25V; C_1206_3216Metric
C41, C47, C150: 1uF; C_0603_1608Metric
C147: 22uF/25V; C_1206_3216Metric
D1: US1D; D_SMA
D10, D23, D24, D25: SS18; D_SMA
J10: Pwr_U; PinHeader_1x03_P2.54mm_Vertical
J11: Gate_H_U; PinHeader_1x03_P2.54mm_Vertical
J12: Gate_L_U; PinHeader_1x03_P2.54mm_Vertical
J13: Ctrl_U; PinHeader_1x03_P2.54mm_Vertical
J15: Sense_U_stack; PinSocket_1x02_P2.54mm_Vertical
R6, R7, R43, R45: 10; R_0805_2012Metric
R8, R9, R44, R46, R58, R59: 10k; R_0603_1608Metric
R102, R103, R104, R105: 2.2; R_0603_1608Metric
U1: IR2110S; SOIC-16W_7.5x10.3mm_P1.27mm

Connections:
3V3_IO: C149.1, C150.1, J10.1, U1.11 (VDD)
12V: C41.2, C47.2, C147.1, C148.1, D1.2 (A), J10.2, U1.3 (VCC)
/Katman2_GateDriver_U/HO_U: R6.1, R43.1, R102.2, R103.2, U1.8 (HO)
/Katman2_GateDriver_U/HO_U_OFF_D10: D10.1 (K), R102.1
/Katman2_GateDriver_U/HO_U_OFF_D23: D23.1 (K), R103.1
/Katman2_GateDriver_U/LO_U: R7.1, R45.1, R104.2, R105.2, U1.1 (LO)
/Katman2_GateDriver_U/LO_U_OFF_D24: D24.1 (K), R104.1
/Katman2_GateDriver_U/LO_U_OFF_D25: D25.1 (K), R105.1
/Katman2_GateDriver_U/VB_U: C1.2, C3.2, D1.1 (K), U1.7 (VB)
GND: C41.1, C47.1, C149.2, C150.2, J10.3, R58.1, R59.2, U1.15 (VSS)
G_UH1: D10.2 (A), J11.1, R6.2, R8.2
G_UH2: D23.2 (A), J11.3, R43.2, R44.2
G_UH_IN: J13.1, R59.1, U1.12 (HIN)
G_UL1: D24.2 (A), J12.1, R7.2, R9.2
G_UL2: D25.2 (A), J12.3, R45.2, R46.2
G_UL_IN: J13.3, R58.2, U1.14 (LIN)
Phase_U: C1.1, C3.1, J11.2, R8.1, R44.1, U1.6 (VS)
SD: J13.2, U1.13 (SD)
USH: C147.2, C148.2, J12.2, R9.1, R46.1, U1.2 (COM)

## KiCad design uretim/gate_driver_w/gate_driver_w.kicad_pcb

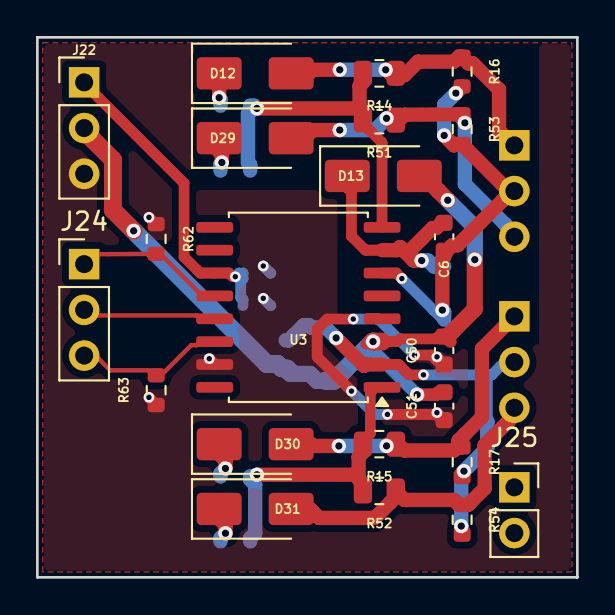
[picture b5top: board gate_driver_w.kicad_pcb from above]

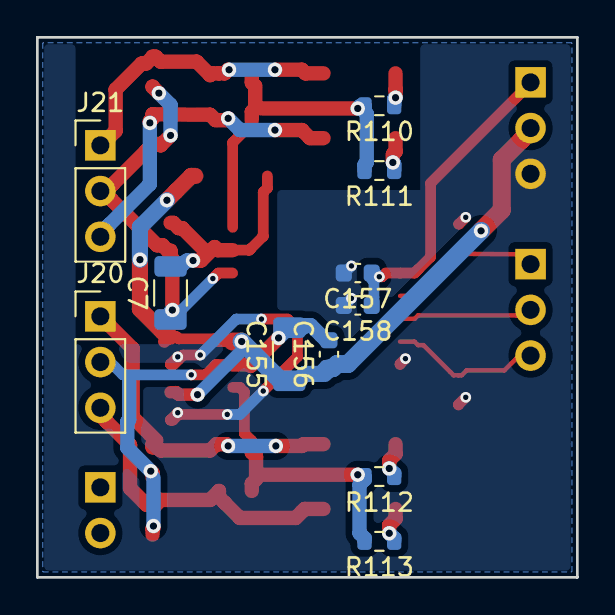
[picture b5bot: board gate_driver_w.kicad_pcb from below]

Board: 2 copper layers, 30.0 x 30.0 mm, 33 parts (11 on the bottom side), 19 nets.

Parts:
C6, C156, C157: 100nF; C_0603_1608Metric
C7: 2.2uF/25V; C_1206_3216Metric
C50, C51, C158: 1uF; C_0603_1608Metric
C155: 22uF/25V; C_1206_3216Metric
D12, D29, D30, D31: SS18; D_SMA
D13: US1D; D_SMA
J20: Gate_L_W; PinHeader_1x03_P2.54mm_Vertical
J21: Gate_H_W; PinHeader_1x03_P2.54mm_Vertical
J22: Pwr_W; PinHeader_1x03_P2.54mm_Vertical
J24: Ctrl_W; PinHeader_1x03_P2.54mm_Vertical
J25: Sense_W_stack; PinSocket_1x02_P2.54mm_Vertical
R14, R15, R51, R52: 10; R_0805_2012Metric
R16, R17, R53, R54, R62, R63: 10k; R_0603_1608Metric
R110, R111, R112, R113: 2.2; R_0603_1608Metric
U3: IR2110S; SOIC-16W_7.5x10.3mm_P1.27mm

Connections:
3V3_IO: C157.1, C158.1, J22.1, U3.11 (VDD)
12V: C50.2, C51.2, C155.1, C156.1, D13.2 (A), J22.2, U3.3 (VCC)
/Katman2_GateDriver_W/HO_W: R14.1, R51.1, R110.2, R111.2, U3.8 (HO)
/Katman2_GateDriver_W/HO_W_OFF_D12: D12.1 (K), R110.1
/Katman2_GateDriver_W/HO_W_OFF_D29: D29.1 (K), R111.1
/Katman2_GateDriver_W/LO_W: R15.1, R52.1, R112.2, R113.2, U3.1 (LO)
/Katman2_GateDriver_W/LO_W_OFF_D30: D30.1 (K), R112.1
/Katman2_GateDriver_W/LO_W_OFF_D31: D31.1 (K), R113.1
/Katman2_GateDriver_W/VB_W: C6.2, C7.2, D13.1 (K), U3.7 (VB)
GND: C50.1, C51.1, C157.2, C158.2, J22.3, R62.2, R63.1, U3.15 (VSS)
G_WH1: D12.2 (A), J21.1, R14.2, R16.2
G_WH2: D29.2 (A), J21.3, R51.2, R53.2
G_WH_IN: J24.1, R62.1, U3.12 (HIN)
G_WL1: D30.2 (A), J20.1, R15.2, R17.2
G_WL2: D31.2 (A), J20.3, R52.2, R54.2
G_WL_IN: J24.3, R63.2, U3.14 (LIN)
Phase_W: C6.1, C7.1, J21.2, R16.1, R53.1, U3.6 (VS)
SD: J24.2, U3.13 (SD)
WSH: C155.2, C156.2, J20.2, R17.1, R54.1, U3.2 (COM)
